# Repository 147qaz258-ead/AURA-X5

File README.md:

# AURA-X5: Embodied Proactive Desktop AI Co-Pilot on D-Robotics RDK X5

> **Robotics Dream Keeper Challenge — 2026 Winter**  
> **Hardware Baseline:** D-Robotics RDK X5 (10 TOPS Bayes BPU + 8-Core Cortex-A55)  
> **License:** MIT ([LICENSE](./LICENSE))  
> **Single Source of Truth (Hardware/Protocol Contract):** [`interfaces.json`](./interfaces.json)

AURA-X5 is a desktop embodied proactive AI agent device powered by **D-Robotics RDK X5**. Instead of running intrusive pop-ups and heavy vision loops on the host PC, AURA-X5 offloads edge perception to the RDK X5 10-TOPS BPU, coordinates subsystems via **ROS 2**, displays non-intrusive proactive suggestions on a dedicated secondary screen (60 FPS HDMI UI or 3.5" SPI touchscreen), and enforces **hardware-level privacy (DPDT physical power-cut)** plus **physical action approval (EC11 rotary encoder / touch + Emergency Kill-Switch)** before injecting any USB-C HID keyboard/mouse actions to the host PC.

---

## Why AURA-X5? (Beyond Stock Demos)

| Pain Point of Software-Only Desktop Agents | AURA-X5 Hardware + Edge-AI Solution |
|---|---|
| Continuous screen/camera perception drains PC GPU/CPU and raises privacy concerns | **10 TOPS BPU offloading** on RDK X5 (`hbm_runtime`) + **DPDT hardware privacy switch** physically severing `V_PRIVACY_3V3` to mic/camera |
| Pop-up notifications interrupt flow on the main monitor | **Dedicated 15° desktop console** (V2 60 FPS HDMI kiosk UI or V1 3.5" 480×320 SPI touch) + WS2812B ambient status ring |
| Software-simulated mouse/keyboard is fragile and lacks a physical e-stop | **USB-C OTG Composite Gadget** (`ecm.usb0` + `/dev/hidg0` + `/dev/hidg1`) gated by **physical approval** and **hardware Kill-Switch (<50 ms abort)** |
| Ad-hoc scripts lack robotic modularity and observability | Full **ROS 2 node graph** (`/aura_sensor_node`, `/aura_bpu_perception_node`, `/aura_safety_gate_node`, `/aura_actuator_ui_bridge_node`) |

---

## Challenge Deliverables Navigation (Stages 1–3)

| Stage | Official Deliverable | Project File |
|---|---|---|
| **Stage 1 — Ignite** | Bring-up, SSH, Sensor/Peripheral Proof, First BPU AI Task | [`docs/STAGE1_IGNITE.md`](./docs/STAGE1_IGNITE.md) |
| **Stage 2 — Build** | Concept & Application Proposal | [`docs/PROPOSAL.md`](./docs/PROPOSAL.md) |
| **Stage 2 — Build** | System Architecture, Compute Plan & ROS 2 Node Graph | [`docs/ARCHITECTURE.md`](./docs/ARCHITECTURE.md) |
| **Stage 2 — Build** | Engineering Plan (Full BOM, Schedule, Top-5 Risks, Repo Layout) | [`docs/ENGINEERING_PLAN.md`](./docs/ENGINEERING_PLAN.md) |
| **Stage 2 — Build** | Public Project Roadmap | [`ROADMAP.md`](./ROADMAP.md) |
| **Stage 3 — Launch** | ROS 2 Package & Launch Files | [`ros2_ws/src/aura_x5_ros/`](./ros2_ws/src/aura_x5_ros/) |
| **Stage 3 — Launch** | Concurrent BPU Benchmark Script & Safety Manual | [`docs/BENCHMARKS_AND_SAFETY.md`](./docs/BENCHMARKS_AND_SAFETY.md) · [`scripts/benchmark_bpu_concurrent.py`](./scripts/benchmark_bpu_concurrent.py) |
| **Hardware (V1 & V2)** | Custom KiCad PCB (0 DRC errors), Gerber, 3D STEP/STL, V2 Solderless HDMI Guide | [`electronics/`](./electronics/) · [`mechanical/`](./mechanical/) · [`docs/02_manufacturing_and_assembly.md`](./docs/02_manufacturing_and_assembly.md) · [`docs/03_hdmi_solderless_guide.md`](./docs/03_hdmi_solderless_guide.md) |
| **Showcase PR** | Official Winter Challenge PR Template (for `D-Robotics/Robotics-Dream-Keeper-Challenge-Winter`) | [`showcase_pr/ParticipantName-Project-AURA-X5.md`](./showcase_pr/ParticipantName-Project-AURA-X5.md) |
| **Community (Advocator)** | External Content Plan (9+ technical posts & videos) | [`docs/ADVOCATOR_CONTENT_PLAN.md`](./docs/ADVOCATOR_CONTENT_PLAN.md) |

---

## Repository Structure

```text
aura_x5/
├── README.md                              # Project overview, quick start & troubleshooting
├── LICENSE                                # MIT License
├── ROADMAP.md                             # Stage 1–3 milestones & task board
├── interfaces.json                        # Hardware pinout (40-pin zero-conflict) & protocol contract
├── docs/
│   ├── STAGE1_IGNITE.md                   # Stage 1 bring-up, sensor & first AI evidence guide
│   ├── PROPOSAL.md                        # Stage 2 concept, users, innovation & measurable goals
│   ├── ARCHITECTURE.md                    # Stage 2 data-flow, module table, BPU/CPU plan & ROS 2 graph
│   ├── ENGINEERING_PLAN.md                # Stage 2 BOM, schedule, top-5 risks & repo plan
│   ├── BENCHMARKS_AND_SAFETY.md           # Stage 3 BPU concurrent benchmarks, calibration & e-stop safety
│   ├── ADVOCATOR_CONTENT_PLAN.md          # Community sharing plan (RDK Advocator / TOP Voice)
│   ├── 01_product_architecture.md         # Original EVT-A hardware architecture
│   ├── 02_manufacturing_and_assembly.md   # EVT-B PCB soldering & 3D print assembly guide
│   ├── 03_hdmi_solderless_guide.md        # V2 HDMI + 40-pin solderless DuPont wiring guide
│   └── evidence/                          # Stage 1–3 screenshots, rqt_graph & benchmark JSONs
├── ros2_ws/
│   └── src/aura_x5_ros/                   # ROS 2 Humble / TogetherROS package
│       ├── aura_x5_ros/
│       │   ├── sensor_node.py             # GPIO / Radar / I2C telemetry & Kill-Switch publisher
│       │   ├── bpu_perception_node.py     # Continuous RDK X5 BPU inference node (hbm_runtime)
│       │   ├── safety_gate_node.py        # Physical-approval & Kill-Switch state machine node
│       │   └── actuator_ui_bridge_node.py # USB-C HID actuator + HDMI/SPI UI bridge node
│       ├── launch/aura_x5.launch.py       # One-command multi-node ROS 2 launch file
│       └── config/aura_x5_params.yaml     # Pinned runtime parameters & safety thresholds
├── firmware/                              # Low-level RDK X5 drivers, BPU service, USB Gadget & UI servers
├── host/                                  # PC companion screen change observer & proactive engine
├── ui_web/                                # Offline self-contained 60 FPS HDMI kiosk web UI
├── electronics/                           # KiCad 9.0.7 schematics/PCB, DRC=0 validation, BOM & Gerber zip
├── mechanical/                            # CadQuery 2.8.0 STEP assembly & watertight 3D-print STLs
├── scripts/                               # Deployment, hardware probe & concurrent BPU benchmark tools
├── verification/                          # Automated unit test suite & physical bring-up checklist
└── showcase_pr/                           # Official challenge repository PR submission file
```

---

## Hardware Editions Supported

1. **Embodied Dual-Eye Companion Prototype (Live Physical Hardware)** — 3D-printed expressive robot head with dual glowing eye displays driven by RDK X5 + dual Espressif ESP32 + Arduino Uno + on-board I2S audio/mic (`docs/evidence/stage1/02a_rdk_x5_hardware_bringup.jpg`, `02b_embodied_dual_eye_prototype.jpg`).
2. **V2 HDMI + Solderless Edition (Fastest Demo & 60 FPS UI)** — Releases 100% of the RDK X5 40-pin header for direct female-to-female DuPont wiring of EC11 encoder, Kill-Switch, DPDT privacy switch, HLK-LD2410C mmWave radar, I2C sensors, and 5V cooling fan, paired with Chromium kiosk 60 FPS HDMI UI (`docs/03_hdmi_solderless_guide.md`).
3. **V1 Custom Carrier HAT (`aura_x5_hat`) + 3.5" SPI Touch + 3D Enclosure** — Complete 2-layer KiCad 9.0.7 PCB (32 parts, 36 nets, 0 DRC errors, Gerber & JLCPCB BOM ready) + 3 watertight CadQuery STL enclosure parts (`docs/02_manufacturing_and_assembly.md`).

| Live RDK X5 Bring-Up | Live 3D-Printed Embodied Dual-Eye Prototype |
|---|---|
|  |  |

---

## Quick Start (Clone, Build, Launch, Stop, Recovery)

### Prerequisites & Pinned Versions
- **RDK X5**: Official RDK OS (Ubuntu 22.04 / Linux 6.1.83), TogetherROS / ROS 2 Humble, `hbm_runtime 1.24.5` (HBRT `3.15.55.0`), Python 3.10+, `websockets`, `numpy`, `pillow`, `smbus2` (optional for I2C), `Hobot.GPIO`.
- **Host PC (Windows 11 / Linux)**: Python 3.10+, `numpy`, `pillow`, `websockets`, `paramiko` (for SSH deployment).
- **Secrets Policy**: Never commit board credentials or API keys. Pass them exclusively via environment variables (`RDK_HOST`, `RDK_USER`, `RDK_PASS`, `MODELSCOPE_API_KEY`).

### 1. Clone & Verify Locally (Host PC)
```bash
git clone https://github.com/147qaz258-ead/AURA-X5.git
cd AURA-X5
python3 verification/test_aura_x5.py
```

### 2. Deploy & Configure USB-C Composite Gadget (RDK X5)
```bash
# On host PC (set env vars first; never hardcode passwords)
export RDK_HOST="192.168.128.10"
export RDK_USER="root"
export RDK_PASS="<your-rdk-password>"
python3 scripts/rdk_probe.py
python3 scripts/deploy_to_rdk.py

# On RDK X5 (optional: enable USB-C RNDIS/ECM + HID keyboard/mouse)
sudo bash /opt/aura_x5/usb_gadget_setup.sh
```

### 3. Build & Launch ROS 2 System (RDK X5)
```bash
source /opt/tros/humble/setup.bash   # or /opt/ros/humble/setup.bash
cd ros2_ws
colcon build --packages-select aura_x5_ros
source install/setup.bash
ros2 launch aura_x5_ros aura_x5.launch.py
```

Open the 60 FPS HDMI kiosk display on RDK X5:
```bash
chromium-browser --kiosk --app=http://127.0.0.1:8080
```

### 4. Start Host PC Proactive Observer
```bash
export AURA_RDK_WS="ws://192.168.128.10:8765"
# Optional LLM context enrichment (runs deterministic rules if unset)
# export MODELSCOPE_API_KEY="<your-key>"
python3 host/pc_live_agent.py
```

### 5. Run Concurrent BPU Benchmark (Stage 3 Evidence)
```bash
# On RDK X5: runs continuous BPU inference + concurrent telemetry/UI loop for 35s
python3 scripts/benchmark_bpu_concurrent.py --duration 35 --out docs/evidence/stage3/bpu_benchmark.json
```

### 6. Safe Stop & Emergency Recovery
- **Emergency Stop (Physical)**: Press the **Kill-Switch** button (GPIO Pin 7). `SafetyGatedAgentCore.trigger_kill_switch()` immediately latches `kill_latched=True`, aborts all pending/active action queues, and writes an 8-byte all-zero release report (`0x00 * 8`) to `/dev/hidg0` so no keys ever stick.
- **Graceful Shutdown**: Press `Ctrl+C` in the `ros2 launch` terminal (node shutdown hooks release HID keys and stop PWM fan/buzzer cleanly).
- **Recovery After Kill-Switch**: Inspect the pending action log, clear the safety latch explicitly via `/aura/reset_kill_latch` ROS 2 service (or restart `safety_gate_node`), and verify `/dev/hidg0` is idle before resuming.

---

## Troubleshooting

| Symptom | Root Cause | Fix |
|---|---|---|
| `BPUUnavailableError: hbm_runtime unavailable` | Running on host PC instead of RDK X5, or model `.bin`/`.hbm` path missing | Run on RDK X5 and confirm model path via `find /app -name '*.bin' -o -name '*.hbm'`. AURA-X5 intentionally fails fast and **never silently falls back to CPU** |
| `PermissionError: Invalid approval source` | Software/remote API attempted to bypass physical approval gate | Approval must originate from `ec11_press`, `xpt2046_touch`, or `hdmi_local_confirm` |
| `/dev/hidg0` missing on RDK X5 | USB-C OTG port not configured in peripheral gadget mode | Ensure USB-C data cable is connected to OTG port and run `sudo bash firmware/usb_gadget_setup.sh` |
| ROS 2 nodes cannot see each other across terminals | ROS 2 environment not sourced or mismatched `ROS_DOMAIN_ID` | Run `source /opt/tros/humble/setup.bash && source ros2_ws/install/setup.bash` in every terminal |
| `No module named 'websockets'` | Missing Python package | `pip3 install websockets numpy pillow` |

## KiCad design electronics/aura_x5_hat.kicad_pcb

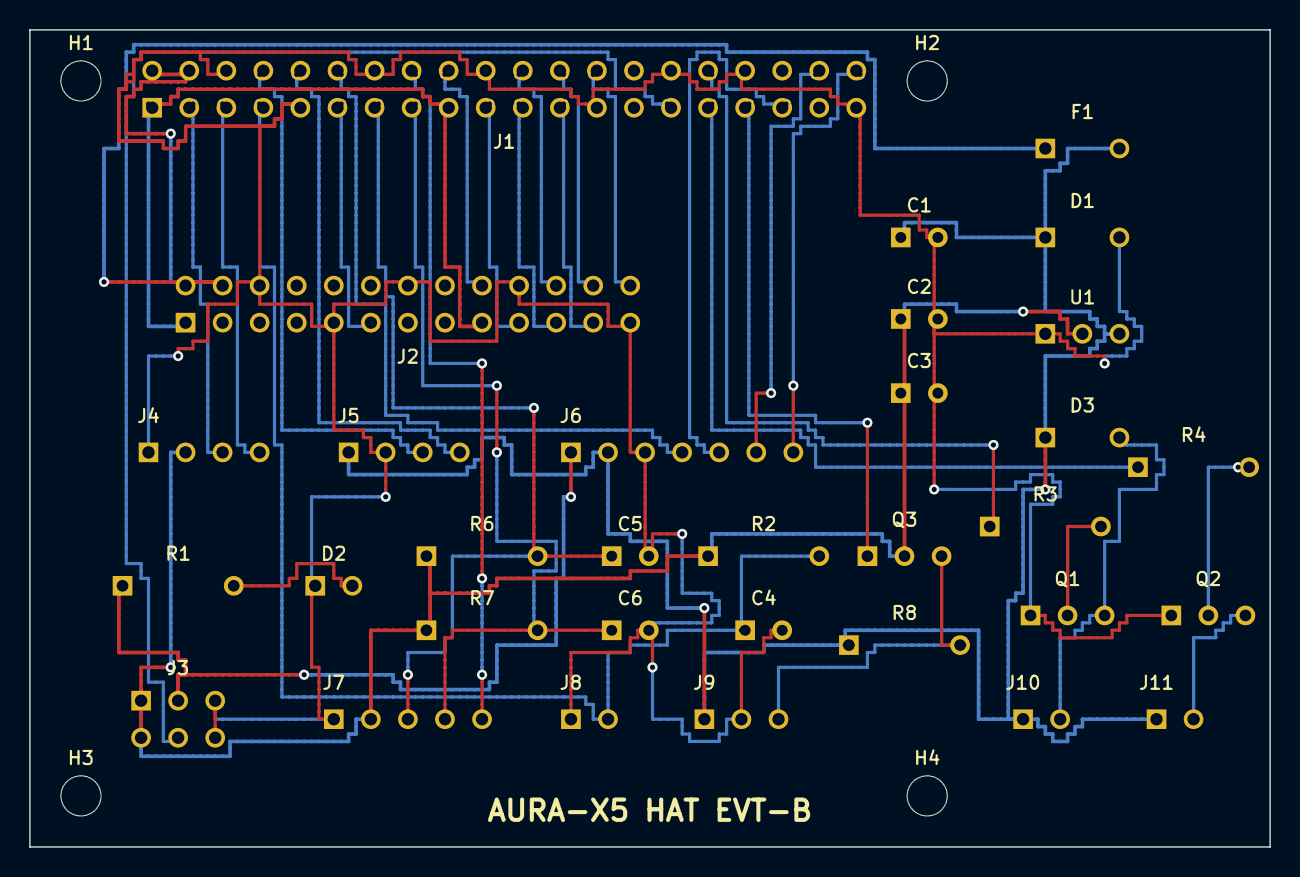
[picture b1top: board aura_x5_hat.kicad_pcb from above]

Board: 2 copper layers, 85.0 x 56.0 mm, 36 parts (0 on the bottom side), 36 nets.

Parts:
C1, C2: 10uF; C_Disc_D3.8mm_W2.6mm_P2.50mm
C3, C4, C5, C6: 100nF; C_Disc_D3.8mm_W2.6mm_P2.50mm
D1: SMBJ5.0A; D_DO-41_SOD81_P5.08mm_Horizontal
D2: PRIV_LED; LED_D3.0mm
D3: 1N4148_FAN; D_DO-41_SOD81_P5.08mm_Horizontal
F1: PTC_3A; Fuse_Bourns_MF-R300
H1, H2, H3, H4: MountingHole_2.7mm_M2.5
J1: RDK_X5_40PIN; PinSocket_2x20_P2.54mm_Vertical
J2: 3.5_TFT_26PIN; PinHeader_2x13_P2.54mm_Vertical
J3: PRIVACY_DPDT; PinHeader_2x03_P2.54mm_Vertical
J4: I2C_BUS; PinHeader_1x04_P2.54mm_Vertical
J5: RADAR_LD2410; PinHeader_1x04_P2.54mm_Vertical
J6: I2S_AUDIO; PinHeader_1x07_P2.54mm_Vertical
J7: EC11_ENC; PinHeader_1x05_P2.54mm_Vertical
J8: KILL_SW; PinHeader_1x02_P2.54mm_Vertical
J9: WS2812_5V; PinHeader_1x03_P2.54mm_Vertical
J10: FAN_5V; PinHeader_1x02_P2.54mm_Vertical
J11: BUZZER_5V; PinHeader_1x02_P2.54mm_Vertical
Q1: 2N3904_FAN; TO-92_Inline_Wide
Q2: 2N3904_BUZ; TO-92_Inline_Wide
Q3: 2N7000_LVL; TO-92_Inline_Wide
R1, R8: 1k; R_Axial_DIN0207_L6.3mm_D2.5mm_P7.62mm_Horizontal
R2, R6, R7: 10k; R_Axial_DIN0207_L6.3mm_D2.5mm_P7.62mm_Horizontal
R3, R4: 680R; R_Axial_DIN0207_L6.3mm_D2.5mm_P7.62mm_Horizontal
U1: AMS1117-3.3; TO-220-3_Vertical

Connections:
+3V3_EXT: C2.1, C3.1, J3.1, J3.4, J4.2, J7.2, Q3.2, R2.1, R6.1, R7.1, U1.2
+3V3_RDK: J1.1, J1.17, J2.1, J2.17
BUZZ_BASE: Q2.2, R4.2
BUZZ_L: J11.2, Q2.3
BUZZ_PWM: J1.31, R4.1
EC11_A: C5.1, J1.13, J7.3, R6.2
EC11_B: C6.1, J1.15, J7.4, R7.2
EC11_SW: J1.16, J7.5
FAN_BASE: Q1.2, R3.2
FAN_L: D3.2, J10.2, Q1.3
FAN_PWM: J1.32, R3.1
GND: C1.2, C2.2, C3.2, C4.2, C5.2, C6.2, D1.2, D2.1, J1.6, J1.9, J1.14, J1.20, J1.25, J1.30, J1.34, J1.39, J2.6, J2.9, J2.14, J2.20, J2.25, J3.3, J3.6, J4.1, J5.2, J6.3, J7.1, J8.1, J9.2, Q1.1, Q2.1, U1.1
I2C_SCL: J1.5, J4.4
I2C_SDA: J1.3, J4.3
I2S_BCLK: J1.12, J6.4
I2S_DIN: J1.38, J6.6
I2S_DOUT: J1.40, J6.7
I2S_LRCLK: J1.35, J6.5
KILL_SW: C4.1, J1.7, J8.2, R2.2
LCD_CS: J1.24, J2.24
LCD_RS: J1.18, J2.18
LCD_RST: J1.22, J2.22
LED_PRIV_A: D2.2, R1.2
PRIV_SENSE: J1.29, J3.5
SPI_MISO: J1.21, J2.21
SPI_MOSI: J1.19, J2.19
SPI_SCK: J1.23, J2.23
TP_CS: J1.26, J2.26
TP_IRQ: J1.11, J2.11
UART_RX: J1.10, J5.4
UART_TX: J1.8, J5.3
V5_PROT: C1.1, D1.1, D3.1, F1.2, J5.1, J6.2, J9.1, J10.1, J11.1, R8.1, U1.3
VBUS_5V: F1.1, J1.2, J1.4, J2.2, J2.4
V_PRIVACY_3V3: J3.2, J6.1, R1.1
WS2812_3V3: J1.33, Q3.1
WS2812_5V: J9.3, Q3.3, R8.2

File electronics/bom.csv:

Reference,Value,MPN,Footprint,Description
J1,RDK_X5_40PIN,Samtec_SSQ-120-03-G-D,Connector_PinSocket_2.54mm:PinSocket_2x20_P2.54mm_Vertical,2x20 2.54mm female stacking header for RDK X5
J2,3.5_TFT_26PIN,PinHeader_2x13_2.54mm,Connector_PinHeader_2.54mm:PinHeader_2x13_P2.54mm_Vertical,2x13 2.54mm header for 3.5inch 480x320 ILI9486+XPT2046 Touch Display
F1,PTC_3A,Bourns_MF-R300,Fuse:Fuse_Bourns_MF-R300,3A Resettable PTC Fuse
D1,SMBJ5.0A,Littelfuse_SMBJ5.0A,Diode_THT:D_DO-41_SOD81_P5.08mm_Horizontal,5V TVS Surge/ESD Protection Diode
U1,AMS1117-3.3,AMS1117-3.3,Package_TO_SOT_THT:TO-220-3_Vertical,Dedicated 3.3V 1A LDO Regulator for peripherals
C1,10uF,Rubycon_10uF_25V,Capacitor_THT:C_Disc_D3.8mm_W2.6mm_P2.50mm,Decoupling capacitor
C2,10uF,Rubycon_10uF_25V,Capacitor_THT:C_Disc_D3.8mm_W2.6mm_P2.50mm,Decoupling capacitor
C3,100nF,KEMET_C315C104K5R5TA,Capacitor_THT:C_Disc_D3.8mm_W2.6mm_P2.50mm,Decoupling capacitor
J3,PRIVACY_DPDT,PinHeader_2x03_2.54mm,Connector_PinHeader_2.54mm:PinHeader_2x03_P2.54mm_Vertical,2x3 header to front panel DPDT Privacy Kill-Switch
R1,1k,MFR-25FBF52-1K,Resistor_THT:R_Axial_DIN0207_L6.3mm_D2.5mm_P7.62mm_Horizontal,Through-hole resistor 0.25W 1%
D2,PRIV_LED,Kingbright_WP710A10ID,LED_THT:LED_D3.0mm,Hardware privacy active indicator LED
J4,I2C_BUS,JST_XH_4P,Connector_PinHeader_2.54mm:PinHeader_1x04_P2.54mm_Vertical,1x4 I2C bus header (VL53L1X + SHT40 + INA219)
J5,RADAR_LD2410,PinHeader_1x04_2.54mm,Connector_PinHeader_2.54mm:PinHeader_1x04_P2.54mm_Vertical,1x4 UART header for HLK-LD2410C 24GHz mmWave Radar
J6,I2S_AUDIO,PinHeader_1x07_2.54mm,Connector_PinHeader_2.54mm:PinHeader_1x07_P2.54mm_Vertical,1x7 I2S Audio header (Mic power gated by hardware privacy switch)
J7,EC11_ENC,PinHeader_1x05_2.54mm,Connector_PinHeader_2.54mm:PinHeader_1x05_P2.54mm_Vertical,1x5 header for front EC11 rotary encoder
R6,10k,MFR-25FBF52-10K,Resistor_THT:R_Axial_DIN0207_L6.3mm_D2.5mm_P7.62mm_Horizontal,Through-hole resistor 0.25W 1%
R7,10k,MFR-25FBF52-10K,Resistor_THT:R_Axial_DIN0207_L6.3mm_D2.5mm_P7.62mm_Horizontal,Through-hole resistor 0.25W 1%
C5,100nF,KEMET_C315C104K5R5TA,Capacitor_THT:C_Disc_D3.8mm_W2.6mm_P2.50mm,Decoupling capacitor
C6,100nF,KEMET_C315C104K5R5TA,Capacitor_THT:C_Disc_D3.8mm_W2.6mm_P2.50mm,Decoupling capacitor
J8,KILL_SW,PinHeader_1x02_2.54mm,Connector_PinHeader_2.54mm:PinHeader_1x02_P2.54mm_Vertical,1x2 header for physical Emergency Kill-Switch button
R2,10k,MFR-25FBF52-10K,Resistor_THT:R_Axial_DIN0207_L6.3mm_D2.5mm_P7.62mm_Horizontal,Through-hole resistor 0.25W 1%
C4,100nF,KEMET_C315C104K5R5TA,Capacitor_THT:C_Disc_D3.8mm_W2.6mm_P2.50mm,Decoupling capacitor
Q3,2N7000_LVL,onsemi_2N7000,Package_TO_SOT_THT:TO-92_Inline_Wide,MOSFET 3.3V->5V level shifter for WS2812B data
R8,1k,MFR-25FBF52-1K,Resistor_THT:R_Axial_DIN0207_L6.3mm_D2.5mm_P7.62mm_Horizontal,Through-hole resistor 0.25W 1%
J9,WS2812_5V,PinHeader_1x03_2.54mm,Connector_PinHeader_2.54mm:PinHeader_1x03_P2.54mm_Vertical,1x3 5V header for 8x WS2812B status ring
J10,FAN_5V,PinHeader_1x02_2.54mm,Connector_PinHeader_2.54mm:PinHeader_1x02_P2.54mm_Vertical,1x2 header for 30x30x7mm 5V PWM cooling fan
R3,680R,MFR-25FBF52-680R,Resistor_THT:R_Axial_DIN0207_L6.3mm_D2.5mm_P7.62mm_Horizontal,Through-hole resistor 0.25W 1%
Q1,2N3904_FAN,onsemi_2N3904BU,Package_TO_SOT_THT:TO-92_Inline_Wide,NPN low-side PWM fan driver
D3,1N4148_FAN,Vishay_1N4148,Diode_THT:D_DO-41_SOD81_P5.08mm_Horizontal,Flyback diode for cooling fan
J11,BUZZER_5V,PinHeader_1x02_2.54mm,Connector_PinHeader_2.54mm:PinHeader_1x02_P2.54mm_Vertical,1x2 header for 5V haptic/alert buzzer
R4,680R,MFR-25FBF52-680R,Resistor_THT:R_Axial_DIN0207_L6.3mm_D2.5mm_P7.62mm_Horizontal,Through-hole resistor 0.25W 1%
Q2,2N3904_BUZ,onsemi_2N3904BU,Package_TO_SOT_THT:TO-92_Inline_Wide,NPN low-side PWM buzzer driver

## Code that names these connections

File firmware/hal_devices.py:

"""Hardware Abstraction Layer (HAL) for AURA-X5 on D-Robotics RDK X5.
Strictly aligned with aura_x5/interfaces.json.
No fake/mock sensor data: raises HardwareUnavailableError when physical buses are absent.
"""
from dataclasses import dataclass
from typing import Optional, Tuple
import struct
import time


class HardwareUnavailableError(RuntimeError):
    """Raised when a required RDK X5 hardware bus or library is not present."""


@dataclass
class RadarReading:
    target_state: int  # 0=none, 1=moving, 2=stationary, 3=both
    moving_dist_cm: int
    moving_energy: int
    static_dist_cm: int
    static_energy: int
    detect_dist_cm: int

    @property
    def user_present(self) -> bool:
        return self.target_state != 0


def parse_ld2410c_frame(frame: bytes) -> Optional[RadarReading]:
    """Parse HLK-LD2410C 24GHz mmWave radar basic data frame (header F4 F3 F2 F1, tail F8 F7 F6 F5)."""
    if len(frame) < 23:
        return None
    if frame[0:4] != b"\xf4\xf3\xf2\xf1" or frame[-4:] != b"\xf8\xf7\xf6\xf5":
        return None
    # Intra-frame: [4:6]=len, [6]=0x02 (normal), [7]=0xAA (head), [8]=target_state
    if frame[6] != 0x02 or frame[7] != 0xAA:
        return None
    target_state = frame[8]
    moving_dist, = struct.unpack_from("<H", frame, 9)
    moving_energy = frame[11]
    static_dist, = struct.unpack_from("<H", frame, 12)
    static_energy = frame[14]
    detect_dist, = struct.unpack_from("<H", frame, 15)
    return RadarReading(
        target_state=target_state,
        moving_dist_cm=moving_dist,
        moving_energy=moving_energy,
        static_dist_cm=static_dist,
        static_energy=static_energy,
        detect_dist_cm=detect_dist,
    )


class XPT2046Touch:
    """4-wire resistive touch controller over GPIO bit-bang (Pins 19/21/23/26/11) on RDK X5."""
    PIN_IRQ = 11
    PIN_MOSI = 19
    PIN_MISO = 21
    PIN_SCLK = 23
    PIN_CS = 26

    def __init__(self, spi_bus: int = 1, spi_dev: int = 1, width: int = 480, height: int = 320):
        self.width = width
        self.height = height
        try:
            import Hobot.GPIO as GPIO  # type: ignore
            self.GPIO = GPIO
            GPIO.setwarnings(False)
            GPIO.setmode(GPIO.BOARD)
            GPIO.setup(self.PIN_MOSI, GPIO.OUT, initial=GPIO.LOW)
            GPIO.setup(self.PIN_SCLK, GPIO.OUT, initial=GPIO.LOW)
            GPIO.setup(self.PIN_CS, GPIO.OUT, initial=GPIO.HIGH)
            GPIO.setup(self.PIN_MISO, GPIO.IN)
            GPIO.setup(self.PIN_IRQ, GPIO.IN)
        except Exception as exc:
            raise HardwareUnavailableError(f"XPT2046 GPIO unavailable: {exc}") from exc

    def _xfer(self, cmd: int) -> int:
        G = self.GPIO
        G.output(self.PIN_CS, G.LOW)
        for i in range(7, -1, -1):
            G.output(self.PIN_MOSI, (cmd >> i) & 1)
            G.output(self.PIN_SCLK, G.HIGH)
            G.output(self.PIN_SCLK, G.LOW)
        val = 0
        for _ in range(16):
            G.output(self.PIN_SCLK, G.HIGH)
            bit = G.input(self.PIN_MISO)
            G.output(self.PIN_SCLK, G.LOW)
            val = (val << 1) | bit
        G.output(self.PIN_CS, G.HIGH)
        return val >> 3

    def is_touched(self) -> bool:
        return self.GPIO.input(self.PIN_IRQ) == 0

    def read_raw(self) -> Tuple[int, int, int]:
        x = self._xfer(0xD0)
        y = self._xfer(0x90)
        z1 = self._xfer(0xB0)
        return x, y, z1

    def read_point(self, z_threshold: int = 60) -> Optional[Tuple[int, int]]:
        x_raw, y_raw, z = self.read_raw()
        if z < z_threshold or x_raw in (0, 4095) or y_raw in (0, 4095):
            return None
        # Landscape 480x320 (ILI9486 MADCTL=0x28): X/Y swapped and X inverted
        px = self.width - 1 - max(0, min(self.width - 1, int((y_raw - 200) * self.width / 3650)))
        py = max(0, min(self.height - 1, int((x_raw - 200) * self.height / 3650)))
        return px, py


class PrivacyAndControls:
    """Manages RDK X5 40-Pin GPIO controls: Privacy Sense, Kill-Switch, EC11, Fan PWM."""
    PIN_KILL_SW = 7
    PIN_EC11_A = 13
    PIN_EC11_B = 15
    PIN_EC11_SW = 16
    PIN_PRIVACY_SENSE = 29
    PIN_BUZZER_PWM = 31
    PIN_FAN_PWM = 32

    def __init__(self):
        try:
            import Hobot.GPIO as GPIO  # type: ignore
            self.GPIO = GPIO
            GPIO.setmode(GPIO.BOARD)
            GPIO.setup(self.PIN_KILL_SW, GPIO.IN)
            GPIO.setup(self.PIN_EC11_A, GPIO.IN)
            GPIO.setup(self.PIN_EC11_B, GPIO.IN)
            GPIO.setup(self.PIN_EC11_SW, GPIO.IN)
            GPIO.setup(self.PIN_PRIVACY_SENSE, GPIO.IN)
            self.fan_pwm = GPIO.PWM(self.PIN_FAN_PWM, 25000)
            self.fan_pwm.start(40)
        except Exception as exc:
            raise HardwareUnavailableError(f"Hobot.GPIO unavailable (not running on RDK X5?): {exc}") from exc

    def is_privacy_power_on(self) -> bool:
        """True if DPDT hardware privacy switch is ON (mic/cam powered), False if physically cut."""
        return bool(self.GPIO.input(self.PIN_PRIVACY_SENSE))

    def is_kill_pressed(self) -> bool:
        return self.GPIO.input(self.PIN_KILL_SW) == 0

    def set_fan_duty(self, pct: int) -> None:
        self.fan_pwm.ChangeDutyCycle(max(0, min(100, int(pct))))
